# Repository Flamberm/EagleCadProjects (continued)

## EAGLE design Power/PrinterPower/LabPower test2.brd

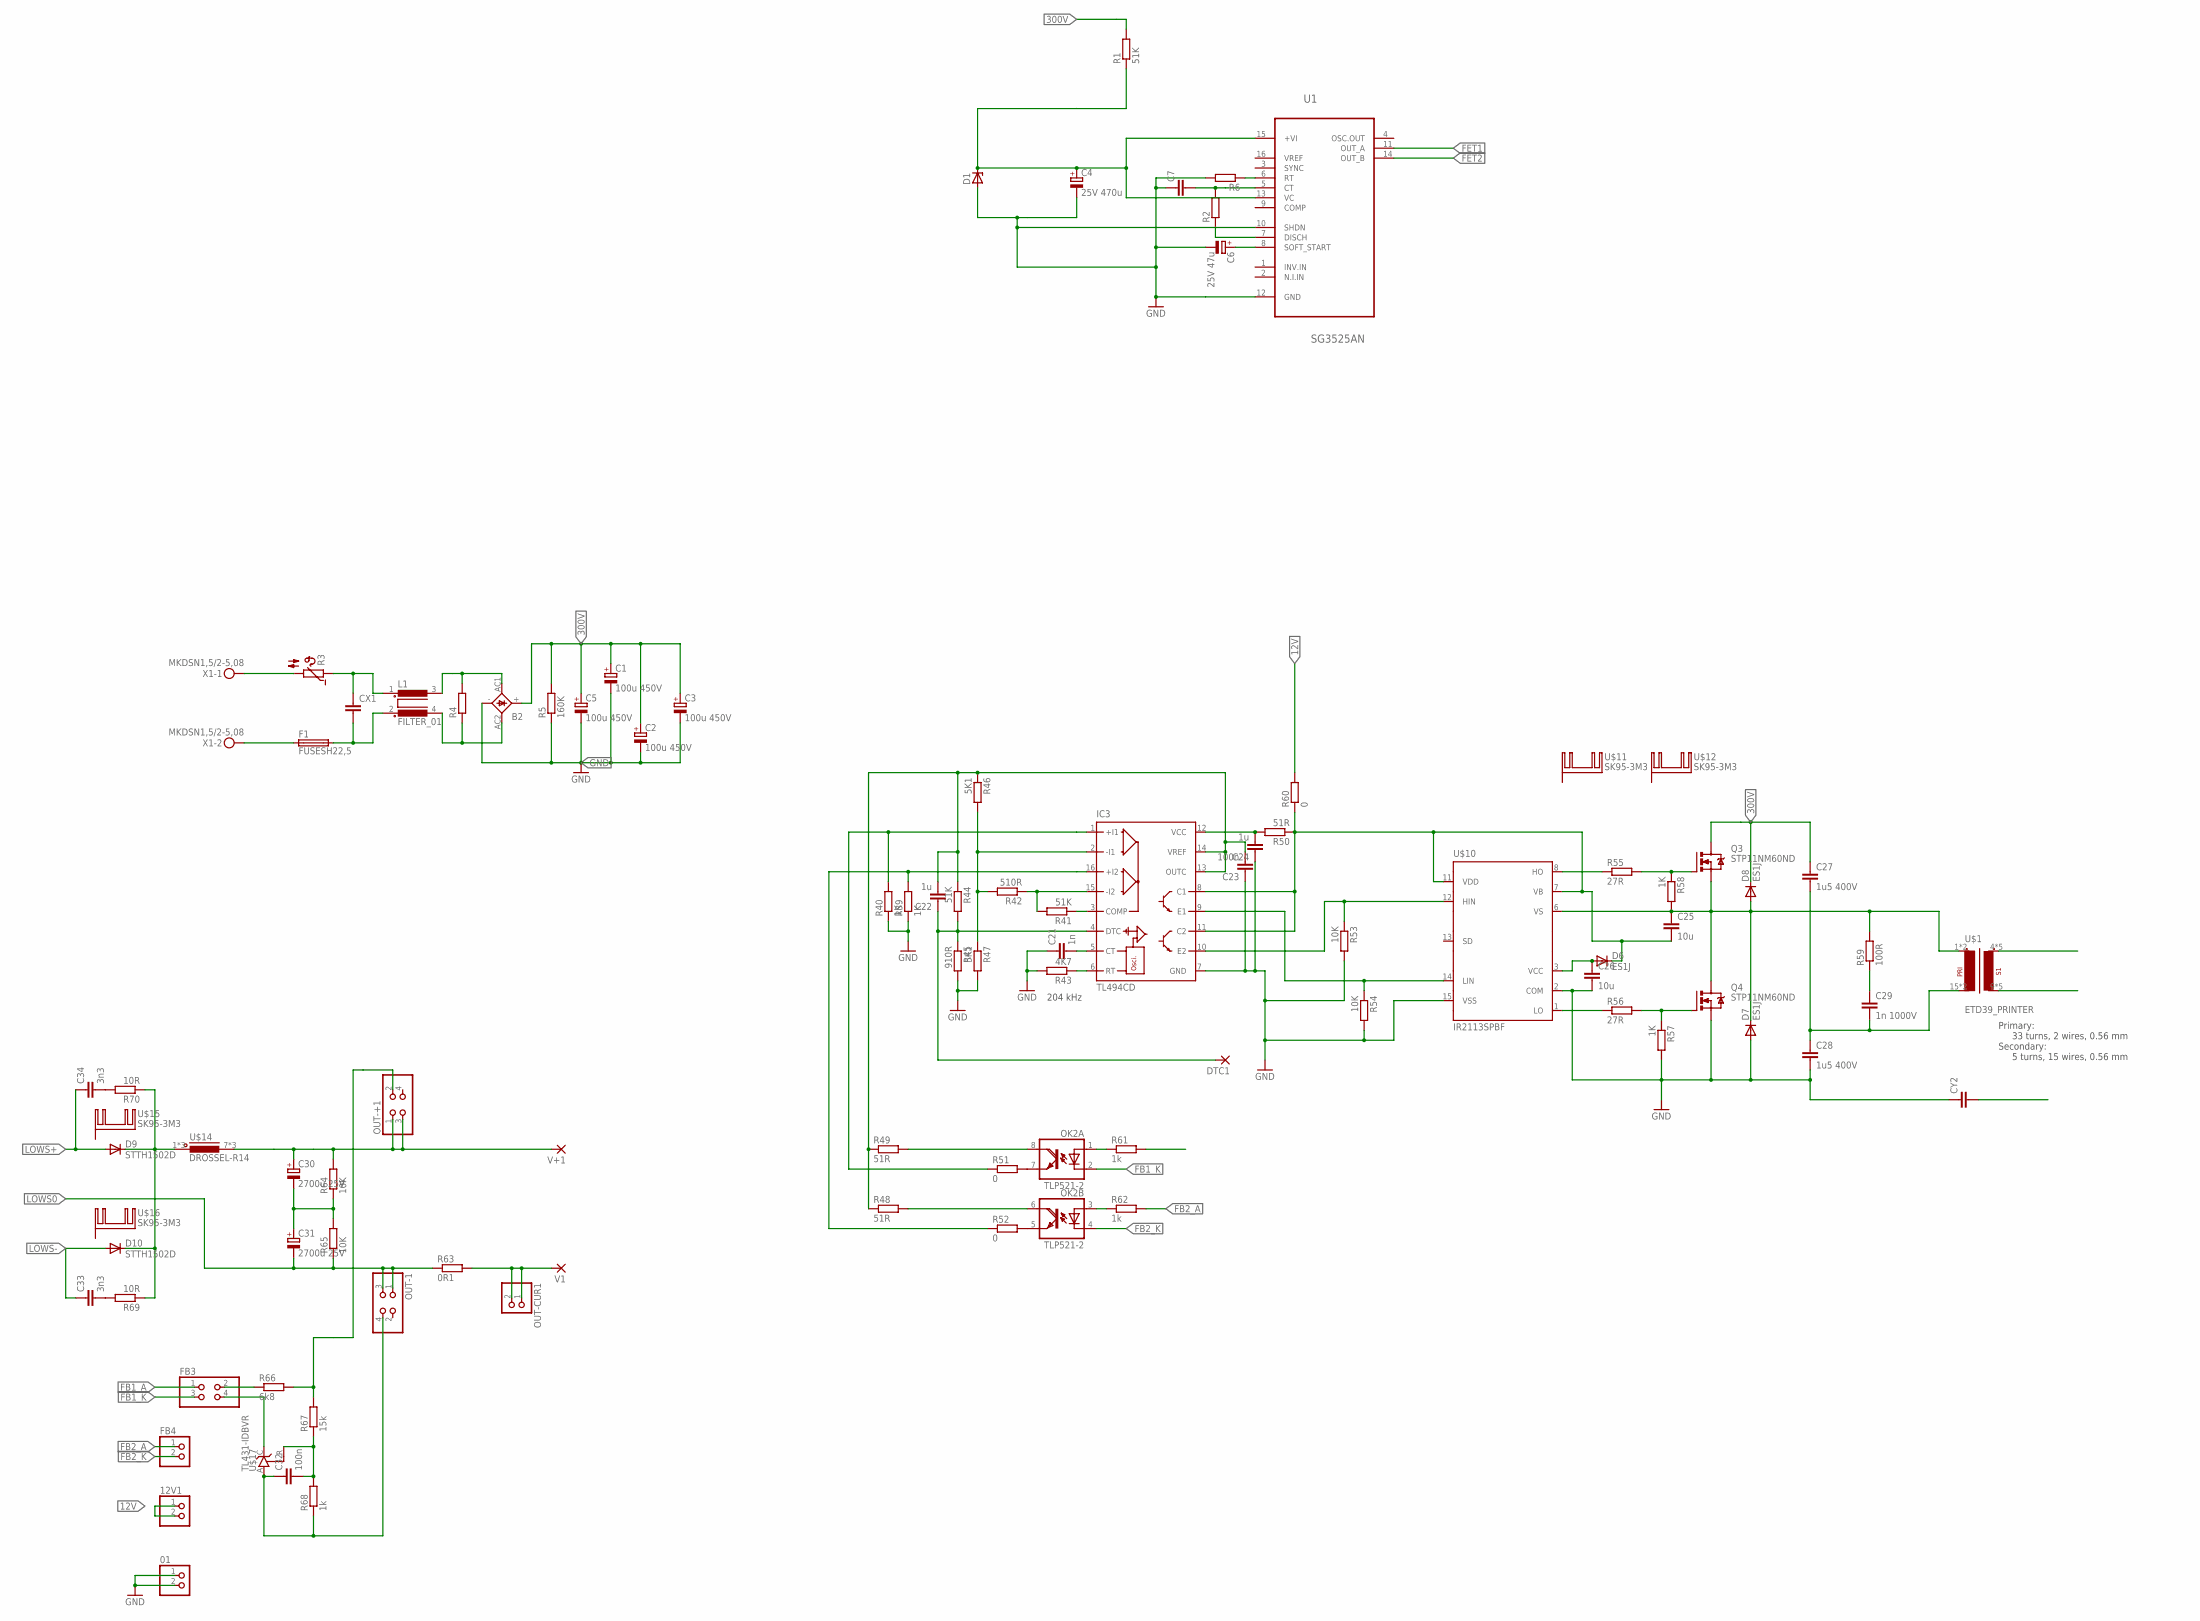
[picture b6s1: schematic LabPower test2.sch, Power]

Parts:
01, 12V1: PINHD-1X2; 1X02
B2: KBL
C1, C2, C3, C5: 100u 450V; EB22,5D
C4: 25V 470u; E2,5-7
C6: 25V 47u; E2,5-7
C7: C-EUC0805; C0805
C21: 1n; C0805
C22, C24: 1u; C0805
C23, C32: 100n; C0805
C25, C26: 10u; C0805
C27, C28: 1u5 400V; C225-087X268
C29: 1n 1000V; C050-025X075
C30, C31: 2700u 25V; E7,5-18
C33, C34: 3n3; C0805
CX1: CXXC15B8; XC15B8
CY2: CYYC10B4; YC10B4
D1: ZENER-DIODEDO41Z10; DO41Z10
D6, D7, D8: ES1J; DO214AC
D9, D10: STTH1502D; DO220S
DTC1: SMD5; SMD2,54-5,08
F1: FUSESH22,5; SH22,5
FB3: PINHD-2X2; 2X02
FB4: PINHD-1X2; 1X02
IC3: TL494CD; SO16
L1: FILTER_01; 82721K
OK2: TLP521-2; DIL08
OUT-1: PINHD-2X2; 2X02
OUT-+1: PINHD-2X2; 2X02
OUT-CUR1: PINHD-1X2; 1X02
Q3, Q4: STP11NM60ND; TO220BV
R1: 51K; SQP-5
R2, R6: R-EU_R0805; R0805
R3: B57164
R4: R-EU_0309/10; 0309/10
R5: 160K; 0207/12
R39, R40, R57, R58: 1K; R0805
R41, R44: 51K; R0805
R42: 510R; R0805
R43: 4K7; R0805
R45: 910R; R0805
R46, R47: 5K1; R0805
R48, R49, R50: 51R; R0805
R51, R52, R60: 0; R1206
R53, R54: 10K; R0805
R55, R56: 27R; R1206
R59: 100R; 0617/17
R61, R62, R68: 1k; R0805
R63: 0R1; SQP-10
R64, R65: 10K; 0207/10
R66: 6k8; R0805
R67: 15k; R0805
R69, R70: 10R; R0805
U1: SG3525AN; DIP254P762X510-16
U$1: ETD39_PRINTER; ETD39_16PIN
U$10: IR2113SPBF; SO16W
U$11, U$12, U$15, U$16: SK95-3M3
U$14: DROSSEL-R14; RM14
U$17: TL431-IDBVR; SOT23-5
V1: 3,81/1,4
V+1: 3,81/1,4
X1: MKDSN1,5/2-5,08

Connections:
12V: 12V1.1, 12V1.2, R60.2
300V: B2.+, C1.+, C2.+, C3.+, C5.+, C27.1, D8.C, Q3.D, R1.2, R5.2
AC1: B2.AC2 (AC1), L1.4, R4.1
AC2: B2.AC1 (AC2), L1.3 (2), R4.2
FB1_A: FB3.1
FB1_A1: R61.2
FB1_K: FB3.3, OK2.2 (C)
FB2_A: FB4.1, R62.2
FB2_K: FB4.2, OK2.4 (C)
FET1: U1.11 (OUT_A)
FET2: U1.14 (OUT_B)
GND: 01.1, 01.2, B2.-, C1.-, C2.-, C3.-, C4.-, C5.-, C6.-, C7.1, C21.1, C23.1, C24.1, C26.2, C28.2, CY2.1, D1.A, D7.A, IC3.7 (GND), Q4.S, R5.1, R6.2, R39.1, R40.1, R43.2, R45.2, R47.2, R53.2, R54.2, R57.2, U1.10 (SHDN), U1.12 (GND), U$10.2 (COM), U$10.15 (VSS)
LOWS0: C31.-, CY2.2, OUT-1.1, OUT-1.3, R63.P$1 (1), R65.1
LOWS+: C34.1, D9.A
LOWS-: C33.1, D10.A
unnamed: U$1.4 (S1-1), U$1.5 (S1-1), U$1.6 (S1-1), U$1.7 (S1-1), U$1.8 (S1-1)
unnamed: U$1.9 (S1-2), U$1.10 (S1-2), U$1.11 (S1-2), U$1.12 (S1-2), U$1.13 (S1-2)
unnamed: C6.+, U1.8 (SOFT_START)
unnamed: C4.+, D1.C, R1.1, U1.13 (VC), U1.15 (+VI)
unnamed: C7.2, R2.2, U1.5 (CT)
unnamed: F1.1, X1.2
unnamed: R3.2, X1.1
unnamed: R2.1, U1.7 (DISCH)
unnamed: CX1.1, L1.1, R3.1
unnamed: CX1.2, F1.2, L1.2 (3)
unnamed: R6.1, U1.6 (RT)
unnamed: IC3.1 (+I1), R40.2, R51.1
unnamed: IC3.16 (+I2), R39.2, R52.1
unnamed: IC3.3 (COMP), R41.1
unnamed: IC3.15 (-I2), R41.2, R42.1
unnamed: IC3.6 (RT), R43.1
unnamed: C21.2, IC3.5 (CT)
unnamed: C22.1, DTC1.1, IC3.4 (DTC), R44.2, R45.1
unnamed: C22.2, C23.2, IC3.13 (OUTC), IC3.14 (VREF), R44.1, R46.1, R48.1, R49.1
unnamed: IC3.2 (-I1), R42.2, R46.2, R47.1
unnamed: OK2.6 (COL), R48.2
unnamed: OK2.8 (COL), R49.2
unnamed: C24.2, IC3.12 (VCC), R50.2
unnamed: IC3.10 (E2), R53.1, U$10.12 (HIN)
unnamed: IC3.9 (E1), R54.1, U$10.14 (LIN)
unnamed: R55.1, U$10.8 (HO)
unnamed: R56.1, U$10.1 (LO)
unnamed: Q4.G, R56.2, R57.1
unnamed: Q3.G, R55.2, R58.1
unnamed: C27.2, C28.1, C29.2, U$1.15 (P1-2), U$1.16 (P1-2)
unnamed: C29.1, R59.1
unnamed: OK2.7 (EMI), R51.2
unnamed: OK2.5 (EMI), R52.2
unnamed: OK2.1 (A), R61.1
unnamed: OK2.3 (A), R62.1
unnamed: D9.C, D10.C, R69.1, R70.1, U$14.1, U$14.2 (1), U$14.3 (1)
unnamed: C30.+, OUT-+1.1, OUT-+1.3, R64.2, U$14.7 (2), U$14.8 (2), U$14.9 (2), V+1.1
unnamed: OUT-CUR1.1, OUT-CUR1.2, R63.P$2 (2), V1.1
unnamed: C30.-, C31.+, R64.1, R65.2
unnamed: FB3.2, R66.1
unnamed: FB3.4, U$17.C
unnamed: C32.1, OUT-1.4, R68.1, U$17.A
unnamed: C32.2, R67.1, R68.2, U$17.R
unnamed: OUT-+1.2, R66.2, R67.2
unnamed: C33.2, R69.2
unnamed: C34.2, R70.2
VB: C25.2, D6.C, IC3.8 (C1), IC3.11 (C2), R50.1, R60.1, U$10.7 (VB), U$10.11 (VDD)
VCC: C26.1, D6.A, U$10.3 (VCC)
VS: C25.1, D7.C, D8.A, Q3.S, Q4.D, R58.2, R59.2, U$1.1 (P1-1), U$1.2 (P1-1), U$10.6 (VS)

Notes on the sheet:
204 kHz
Primary: 33 turns, 2 wires, 0.56 mm Secondary: 5 turns, 15 wires, 0.56 mm

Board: 2 copper layers, 94 parts (0 on the bottom side), 60 nets, no tracks yet.

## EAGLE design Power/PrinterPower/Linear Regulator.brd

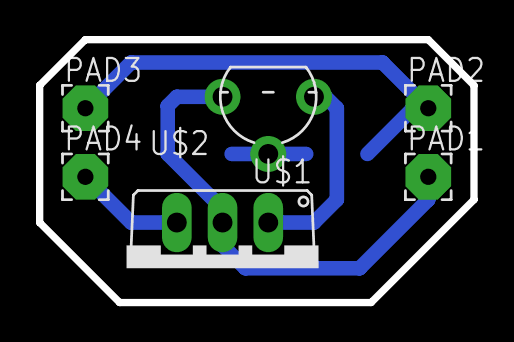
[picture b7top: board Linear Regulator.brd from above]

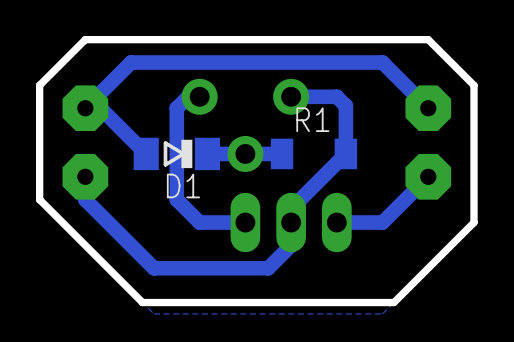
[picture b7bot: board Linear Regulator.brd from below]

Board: 2 copper layers, 24.1 x 14.6 mm, 8 parts (2 on the bottom side), 5 nets.

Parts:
D1: 15V; SOD80C
PAD1, PAD2, PAD3, PAD4: 2,54/0,9
R1: R1206
U$1: MFR475V; TO220AV
U$2: KSP42TA; SOT-92WIDE

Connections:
unnamed: D1.C, R1.1, U$2.B
unnamed: PAD1.1, R1.2, U$1.C, U$2.C
unnamed: U$1.B, U$2.E
unnamed: PAD4.1, U$1.E
unnamed: D1.A, PAD2.1, PAD3.1
